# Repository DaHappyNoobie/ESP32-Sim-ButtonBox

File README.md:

## ESP32 Sim Buttonbox
I got into flying IL-2 Great Battles pretty recently, and found myself needing a lot of buttons for control surfaces trimming, engine controls, radiators, etc...
Not enough buttons on my stick and throttle, and using keyboard is annoying! I need a button box! Good opportunity for a small personal project and learning a bit about building devices in an enclosure like this.
Time to make a simple but usable USB button box.

## What it does
This box exposes 9 bidirectional momentary switches, 8 toggle switches, and a button (27 GPIOs total). It uses an ESP32-S3 microcontroller implementing the TinyUSB stack with HID gamepad profile. This allows the box to be plug-and-play into any USB host, without the need for drivers. The circuit board and firmware are intended to be either reused as-is in other configurations, or expanded upon for more complex button boxes.

## Firmware
Written using ESP-IDF v5.5.1 framework. Install that either independently or through the VSCode extension, build,, flash, restart the board, and the USB controller should pop up in your PC's peripherals, ready to use.
The firmware itself is simple, derived from the TinyUSb HID example in ESP-IDF. A simple polling loop handles reading all the inputs, then building and sending a HID report through USB. Provisions are made in hardware to use the I/Os in Interrupt mode instead of polling (even through the I²C GPIO expander), but it's not really needed for my current use.
Keep the small Boot button pressed on the board while plugging the USB in to boot up in firmware download mode and reprogram the board if needed.

## Hardware
I designed a small 2-layer PCB implementing everything that's needed for a generic button box controller. Hook up your buttons and switches to the screw terminals on the board and start building.
The USB-B receptacle sticks out the back of the PCB, as it is intended to be mounted against the rear face of the enclosure.
I used a Hammond 1456CE3BKBU aluminium enclosure to build this project. It's relatively cheap, easy to work on, and has the perfect form factor for my space-constrained requirements.

MECHANICAL_ASSEMBLY folder contains 3D models in.step format for the following elements :
- Bare enclosure as sold
- Enclosure with the necessary drill holes for buttons, switches and mounting
- Controller circuit board
- Fully assembled button box (with all independent parts embedded in the file)

PCB_ESP32_SimButtonBox folder contains the circuit board design files :
- Parts BOM
- Autodesk EAGLE CAD files in .sch and .brd formats. Since EAGLE is now discontinued, you should be able to import them in Fusion360 Electronics with no issue. KiCAD should work too!
- Schematic in PDF format
- Gerber files for manufacturing the PCBs. I recommend getting a small solder stencil according to the Gerbers for easier reflow soldering.

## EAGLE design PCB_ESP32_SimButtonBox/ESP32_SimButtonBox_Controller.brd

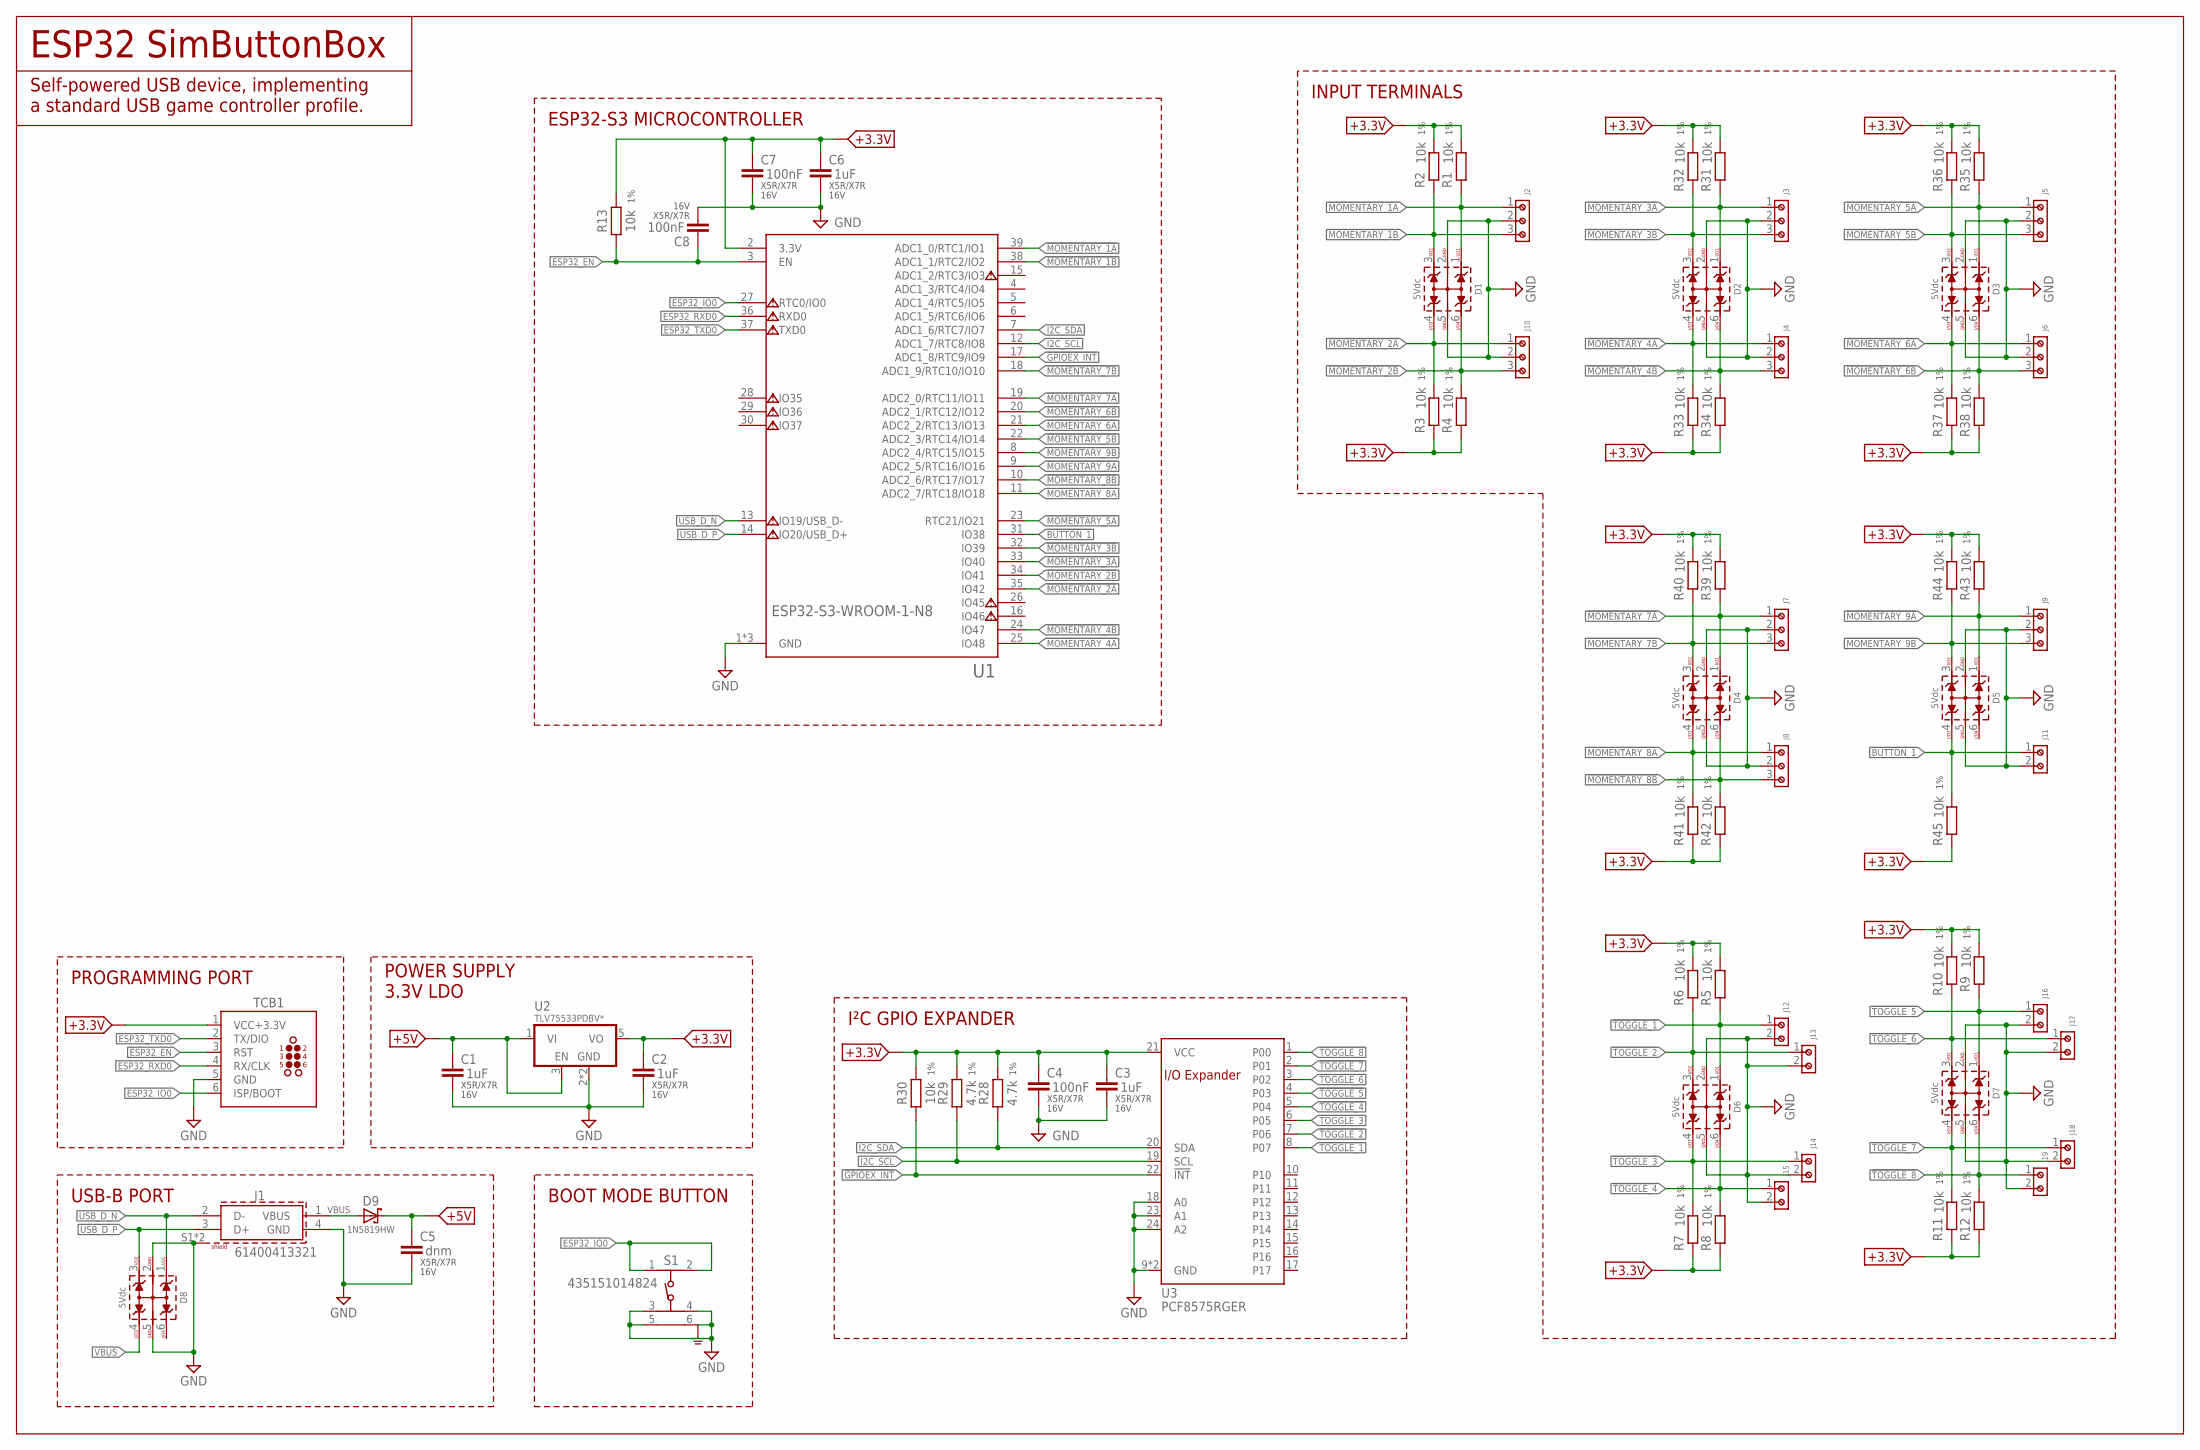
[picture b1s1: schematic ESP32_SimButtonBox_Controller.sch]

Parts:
C1, C2, C3, C6: 1uF; C0603; VOLTAGE 16V
C4, C7, C8: 100nF; C0603; VOLTAGE 16V
C5: dnm; C0603; VOLTAGE 16V
D1, D2, D3, D4, D5, D6, D7, D8: 5Vdc; WE-TVS_SOT23-6L
D9: 1N5819HW; SOD123
J1: 61400413321
J2, J3, J4, J5, J6, J7, J8, J9, J10: 691210910003
J11, J12, J13, J14, J15, J16, J17, J18, J19: 691210910002
R1, R2, R3, R4, R5, R6, R7, R8, R9, R10, R11, R12, R13, R30, R31, R32, R33, R34, R35, R36, R37, R38, R39, R40, R41, R42, R43, R44, R45: 10k; R0603
R28, R29: 4.7k; R0603
S1: 435151014824
TCB1: TC2030-MCP-NL
U1: ESP32-S3-WROOM-1-N8; WROOM-1
U2: LDO_EN_SOT23-5; SOT23-5
U3: PCF8575RGE; QFN50P400X400X100-25T210N

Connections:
!BUTTON_1: D5.4 (3), J11.1, R45.2, U1.31 (IO38)
!GPIOEX_INT: R30.1, U1.17 (ADC1_8/RTC9/IO9), U3.22 (!INT)
!MOMENTARY_1A: D1.1, J2.1, R1.1, U1.39 (ADC1_0/RTC1/IO1)
!MOMENTARY_1B: D1.3 (2), J2.3, R2.1, U1.38 (ADC1_1/RTC2/IO2)
!MOMENTARY_2A: D1.4 (3), J10.1, R3.2, U1.35 (IO42)
!MOMENTARY_2B: D1.6 (4), J10.3, R4.2, U1.34 (IO41)
!MOMENTARY_3A: D2.1, J3.1, R31.1, U1.33 (IO40)
!MOMENTARY_3B: D2.3 (2), J3.3, R32.1, U1.32 (IO39)
!MOMENTARY_4A: D2.4 (3), J4.1, R33.2, U1.25 (IO48)
!MOMENTARY_4B: D2.6 (4), J4.3, R34.2, U1.24 (IO47)
!MOMENTARY_5A: D3.1, J5.1, R35.1, U1.23 (RTC21/IO21)
!MOMENTARY_5B: D3.3 (2), J5.3, R36.1, U1.22 (ADC2_3/RTC14/IO14)
!MOMENTARY_6A: D3.4 (3), J6.1, R37.2, U1.21 (ADC2_2/RTC13/IO13)
!MOMENTARY_6B: D3.6 (4), J6.3, R38.2, U1.20 (ADC2_1/RTC12/IO12)
!MOMENTARY_7A: D4.1, J7.1, R39.1, U1.19 (ADC2_0/RTC11/IO11)
!MOMENTARY_7B: D4.3 (2), J7.3, R40.1, U1.18 (ADC1_9/RTC10/IO10)
!MOMENTARY_8A: D4.4 (3), J8.1, R41.2, U1.11 (ADC2_7/RTC18/IO18)
!MOMENTARY_8B: D4.6 (4), J8.3, R42.2, U1.10 (ADC2_6/RTC17/IO17)
!MOMENTARY_9A: D5.1, J9.1, R43.1, U1.9 (ADC2_5/RTC16/IO16)
!MOMENTARY_9B: D5.3 (2), J9.3, R44.1, U1.8 (ADC2_4/RTC15/IO15)
!TOGGLE_1: D6.1, J12.1, R5.1, U3.8 (P07)
!TOGGLE_2: D6.3 (2), J13.1, R6.1, U3.7 (P06)
!TOGGLE_3: D6.4 (3), J14.1, R7.2, U3.6 (P05)
!TOGGLE_4: D6.6 (4), J15.1, R8.2, U3.5 (P04)
!TOGGLE_5: D7.1, J16.1, R9.1, U3.4 (P03)
!TOGGLE_6: D7.3 (2), J17.1, R10.1, U3.3 (P02)
!TOGGLE_7: D7.4 (3), J18.1, R11.2, U3.2 (P01)
!TOGGLE_8: D7.6 (4), J19.1, R12.2, U3.1 (P00)
+3.3V: C2.1, C3.1, C4.1, C6.1, C7.1, R1.2, R2.2, R3.1, R4.1, R5.2, R6.2, R7.1, R8.1, R9.2, R10.2, R11.1, R12.1, R13.2, R28.2, R29.2, R30.2, R31.2, R32.2, R33.1, R34.1, R35.2, R36.2, R37.1, R38.1, R39.2, R40.2, R41.1, R42.1, R43.2, R44.2, R45.1, TCB1.1 (VCC+3.3V), U1.2 (3.3V), U2.5 (VO), U3.21 (VCC)
+5V: C1.1, C5.1, D9.C, U2.1 (VI), U2.3 (EN)
ESP32_EN: C8.1, R13.1, TCB1.3 (RST), U1.3 (EN)
ESP32_IO0: S1.1, S1.2, TCB1.6 (ISP/BOOT), U1.27 (RTC0/IO0)
ESP32_RXD0: TCB1.4 (RX/CLK), U1.36 (RXD0)
ESP32_TXD0: TCB1.2 (TX/DIO), U1.37 (TXD0)
GND: C1.2, C2.2, C3.2, C4.2, C5.2, C6.2, C7.2, C8.2, D1.2 (GND), D1.5 (GND), D2.2 (GND), D2.5 (GND), D3.2 (GND), D3.5 (GND), D4.2 (GND), D4.5 (GND), D5.2 (GND), D5.5 (GND), D6.2 (GND), D6.5 (GND), D7.2 (GND), D7.5 (GND), D8.2 (GND), D8.5 (GND), J1.4 (GND), J1.S1 (SHIELD), J1.S2 (SHIELD), J2.2, J3.2, J4.2, J5.2, J6.2, J7.2, J8.2, J9.2, J10.2, J11.2, J12.2, J13.2, J14.2, J15.2, J16.2, J17.2, J18.2, J19.2, S1.3, S1.4, S1.5, S1.6, TCB1.5 (GND), U1.1 (GND), U1.40 (GND), U1.P$1 (GND), U2.2 (GND), U2.4 (GND), U3.9 (GND), U3.18 (A0), U3.23 (A1), U3.24 (A2), U3.25 (GND)
I2C_SCL: R29.1, U1.12 (ADC1_7/RTC8/IO8), U3.19 (SCL)
I2C_SDA: R28.1, U1.7 (ADC1_6/RTC7/IO7), U3.20 (SDA)
USB_D_N: D8.1, J1.2 (D-), U1.13 (IO19/USB_D-)
USB_D_P: D8.3 (2), J1.3 (D+), U1.14 (IO20/USB_D+)
VBUS: D8.4 (3), D9.A, J1.1 (VBUS)

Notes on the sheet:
ESP32-S3 MICROCONTROLLER
PROGRAMMING PORT
POWER SUPPLY 3.3V LDO
I²C GPIO EXPANDER
USB-B PORT
BOOT MODE BUTTON
INPUT TERMINALS
ESP32 SimButtonBox
Self-powered USB device, implementing a standard USB game controller profile.

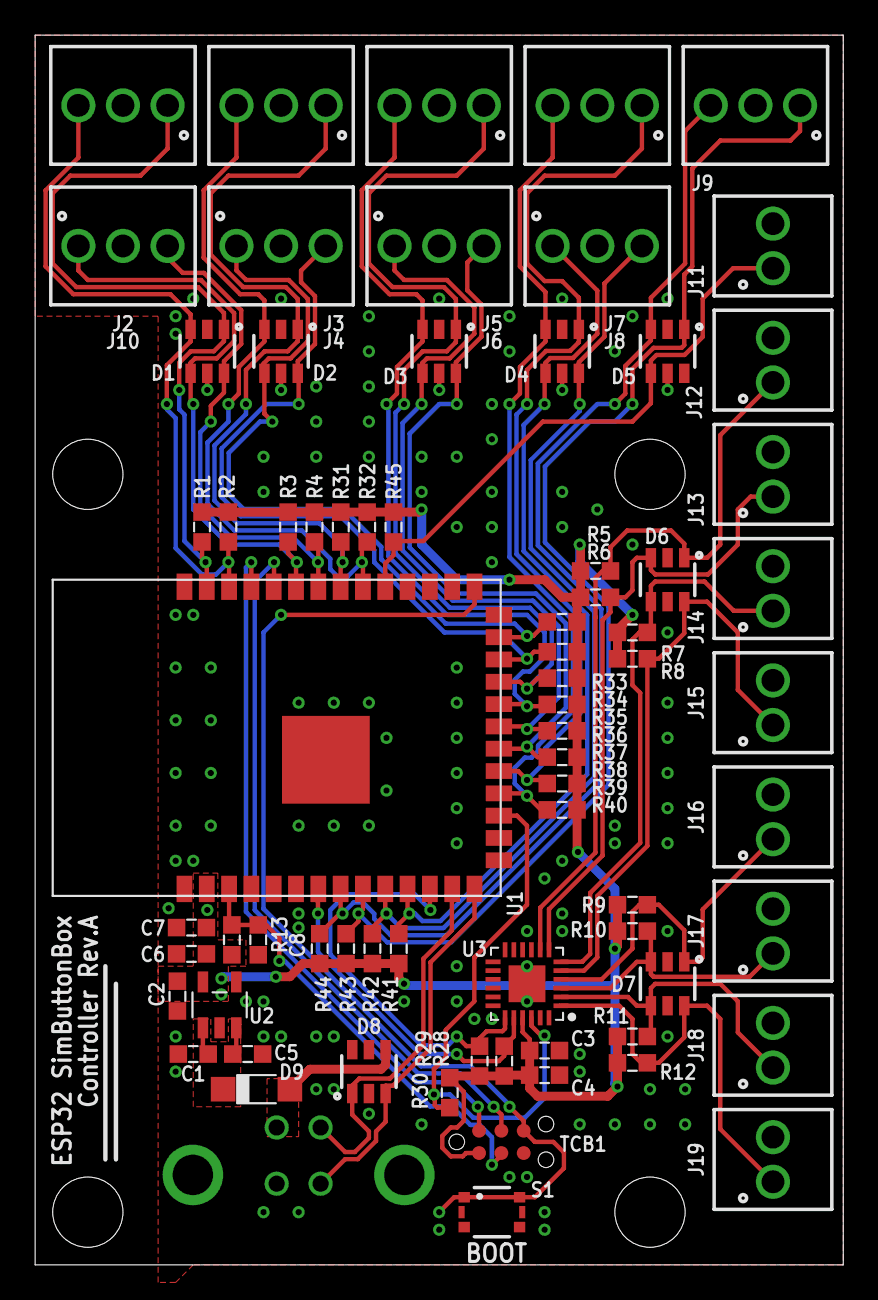
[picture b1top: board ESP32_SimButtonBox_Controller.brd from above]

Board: 2 copper layers, 46.0 x 70.0 mm, 73 parts (1 on the bottom side), 40 nets.

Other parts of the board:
U$1: PCB-SPEC

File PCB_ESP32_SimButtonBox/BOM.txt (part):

Partlist exported from C:/Users/HugoCuzon/Documents/Perso-3D/ESP32_SimButtonBox/ESP32_SimButtonBox_Controller.sch at 18/02/2026 12:15

Qty Value               Device                   Package                   Parts                                                                                                                                  Description                                               ALTERNATE APPLICATION BOM_CAT C-CH CHANNELS CROSS-REF CROSSREFS CURRENT DATASHEET-URL                                                 DESCRIPTION                                                               EQUIVALENCE GERDER     H     INTERFACE-TYPE IOUT  IPEAK IR-UL IR1  ISHDN MATERIAL MF                MOUNT MP                  NOT_IN_BOM OPERATION-FORCE PACKAGING PINS PITCH  POL POPULARITY POWER REF-EXCALIBUR REF_EXCALIBUR TOLERANCE TYPE       VALUE         VBR VMAX VMIN  VOLTAGE WIRE                                 WORKING-VOLTAGE WORKING-VOLTAGE-UL
9                       691210910002             691210910002              J11, J12, J13, J14, J15, J16, J17, J18, J19                                                                                            WR-TBL Serie 2109 - 2.54 mm Horiz. Entry                                                                                          https://www.we-online.com/catalog/datasheet/691210910002.pdf  WR-TBL Rising Cage Clamp                                                                                                          6A                        Wurth Elektronik  THT    691210910002                                             2   2.54mm                                                            Horizontal                                      30 to 18 (AWG) 0.0509 to 0.823 (mm²)                 150V (AC)         
9                       691210910003             691210910003              J2, J3, J4, J5, J6, J7, J8, J9, J10                                                                                                    WR-TBL Serie 2109 - 2.54 mm Horiz. Entry                                                                                          https://www.we-online.com/catalog/datasheet/691210910003.pdf  WR-TBL Rising Cage Clamp                                                                                                          6A                        Wurth Elektronik  THT    691210910003                                             3   2.54mm                                                            Horizontal                                      30 to 18 (AWG) 0.0509 to 0.823 (mm²)                 150V (AC)         
3   100nF               CAP_0603                 C0603                     C4, C7, C8                                                                                                                             Capacitor                                                                       C_SMD                                                                                                                                                                                                                                                              X5R/X7R                                                                                                                                                                                                  16V                                                                            
29  10k                 RES_0603                 R0603                     R1, R2, R3, R4, R5, R6, R7, R8, R9, R10, R11, R12, R13, R30, R31, R32, R33, R34, R35, R36, R37, R38, R39, R40, R41, R42, R43, R44, R45 Resistor                                                                        R_SMD                                                                                                                                                                                                                                                                                                                                                                        80                                           1%                                                                                                                               
1   1N5819HW            SCHOTTKY_SOD123          SOD123                    D9                                                                                                                                     Schottky Diode                                                                                                            1A                                                                    Schottky diode                                                                                                                                                                      1N5819HW                                                                                                                                                                                                                                               
4   1uF                 CAP_0603                 C0603                     C1, C2, C3, C6                                                                                                                         Capacitor                                                                       C_SMD                                                                                                                                                                                                                                                              X5R/X7R                                                                                                                                                                                                  16V                                                                            
2   4.7k                RES_0603                 R0603                     R28, R29                                                                                                                               Resistor                                                                        R_SMD                                                                                                                                                                                                                                                                                                                                                                        80                                           1%                                                                                                                               
1   435151014824        435151014824             435151014824              S1                                                                                                                                     WS-TASV SMT Tact Switch 3.0 x 2.6 mm with ground terminal                                                                         https://www.we-online.com/catalog/datasheet/435151014824 .pdf WS-TASV Switches - Tact Switches                                                                 1.4mm                                                      Wurth Elektronik        435151014824                   240g                                                                                                        435151014824                                                                                                
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
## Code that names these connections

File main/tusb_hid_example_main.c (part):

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#include <pcf8575.h>

// I²C lines for GPIO Expander
#define PIN_I2C_SDA (GPIO_NUM_7)
#define PIN_I2C_SCL (GPIO_NUM_8)
#define PIN_I2C_INT (GPIO_NUM_9)
#define I2C_ADDR 0x20 //7-bit address of GPIO Expander
// MCU inputs
#define MOMENTARY_1A  (GPIO_NUM_1)
#define MOMENTARY_1B  (GPIO_NUM_2)
#define MOMENTARY_2A  (GPIO_NUM_42)
#define MOMENTARY_2B  (GPIO_NUM_41)
#define MOMENTARY_3A  (GPIO_NUM_40)
#define MOMENTARY_3B  (GPIO_NUM_39)
#define MOMENTARY_4A  (GPIO_NUM_48)
#define MOMENTARY_4B  (GPIO_NUM_47)
#define MOMENTARY_5A  (GPIO_NUM_21)
#define MOMENTARY_5B  (GPIO_NUM_14)
#define MOMENTARY_6A  (GPIO_NUM_13)
#define MOMENTARY_6B  (GPIO_NUM_12)
#define MOMENTARY_7A  (GPIO_NUM_11)
#define MOMENTARY_7B  (GPIO_NUM_10)
#define MOMENTARY_8A  (GPIO_NUM_18)
#define MOMENTARY_8B  (GPIO_NUM_17)
#define MOMENTARY_9A  (GPIO_NUM_16)
#define MOMENTARY_9B  (GPIO_NUM_15)
#define PUSHBUTTON    (GPIO_NUM_38)

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    ESP_ERROR_CHECK(i2cdev_init());
    i2c_dev_t pcf8575;
    memset(&pcf8575, 0, sizeof(i2c_dev_t));
    ESP_ERROR_CHECK(pcf8575_init_desc(&pcf8575, I2C_ADDR, 0, PIN_I2C_SDA, PIN_I2C_SCL));
    uint16_t gpioExpanderPortVal = 0xFFFF;

    ESP_LOGI(TAG, "USB initialization");
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            }
            // Get IO states and build report
            gamepad_report.buttons = 0;
            if(!gpio_get_level(MOMENTARY_1A)){
                gamepad_report.buttons += GAMEPAD_BUTTON_0;
            } if(!gpio_get_level(MOMENTARY_1B)){
                gamepad_report.buttons += GAMEPAD_BUTTON_1;
            } if(!gpio_get_level(MOMENTARY_2A)){
                gamepad_report.buttons += GAMEPAD_BUTTON_2;
            } if(!gpio_get_level(MOMENTARY_2B)){
                gamepad_report.buttons += GAMEPAD_BUTTON_3;
            } if(!gpio_get_level(MOMENTARY_3A)){
                gamepad_report.buttons += GAMEPAD_BUTTON_4;
            } if(!gpio_get_level(MOMENTARY_3B)){
                gamepad_report.buttons += GAMEPAD_BUTTON_5;
            } if(!gpio_get_level(MOMENTARY_4A)){
                gamepad_report.buttons += GAMEPAD_BUTTON_6;
            } if(!gpio_get_level(MOMENTARY_4B)){
                gamepad_report.buttons += GAMEPAD_BUTTON_7;
            } if(!gpio_get_level(MOMENTARY_5A)){
                gamepad_report.buttons += GAMEPAD_BUTTON_8;
            } if(!gpio_get_level(MOMENTARY_5B)){
                gamepad_report.buttons += GAMEPAD_BUTTON_9;
            } if(!gpio_get_level(MOMENTARY_6A)){
                gamepad_report.buttons += GAMEPAD_BUTTON_10;
            } if(!gpio_get_level(MOMENTARY_6B)){
                gamepad_report.buttons += GAMEPAD_BUTTON_11;
            } if(!gpio_get_level(MOMENTARY_7A)){
                gamepad_report.buttons += GAMEPAD_BUTTON_12;
            } if(!gpio_get_level(MOMENTARY_7B)){
                gamepad_report.buttons += GAMEPAD_BUTTON_13;
            } if(!gpio_get_level(MOMENTARY_8A)){
                gamepad_report.buttons += GAMEPAD_BUTTON_14;
            } if(!gpio_get_level(MOMENTARY_8B)){
                gamepad_report.buttons += GAMEPAD_BUTTON_15;
            } if(!gpio_get_level(MOMENTARY_9A)){
                gamepad_report.buttons += GAMEPAD_BUTTON_16;
            } if(!gpio_get_level(MOMENTARY_9B)){
                gamepad_report.buttons += GAMEPAD_BUTTON_17;
            } if(!gpio_get_level(PUSHBUTTON)){
                gamepad_report.buttons += GAMEPAD_BUTTON_18;
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
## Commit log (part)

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2025-12-25 Update LICENSE
2025-12-25 Imported USB HID example from ESP-IDF
2025-12-25 Listed necessary inputs
2025-12-30 GAmepad reported OK with 1 button in polling mode
2025-12-30 Use proper gamepad report struct for values, still polling
2026-03-22 Full (polling) implementation of PCB with IOexp
2026-03-22 Fixed missing pushbutton definition

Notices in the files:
parts and their libraries:
Wurth_Connectors_WR-TBL Rising Cage Clam: Copyright: Würth Elektronik
